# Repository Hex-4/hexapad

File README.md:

# Hexapad

A DIY macropad made for the [Hack Club](https://hack.club) [Hackpad](https://hackpad.hackclub.com) program! It's got 16 Cherry MX switches, a "jewel" of 3 THT NeoPixels, a rotary encoder, and an OLED screen. A I/O expander is used to make everything work. This repo holds the PCB design, case design, and KMK firmware.

## Making it

This was my _first time_ doing... most of this. I've dabbled in mechanical keyboards before (I'm typing this on one right now!) but I've never touched PCB design or CAD. Therefore, I made the perfectly rational decision to YOLO it and try not to mess up. Thankfully, it went quite well! I think. I picked up KiCad really quickly, and the community (#hackpad on the Hack Club Slack) was super helpful. OnShape was harder to grasp but I think I kinda get it now? The firmware was super easy thanks to KMK, all I really had to do was paste in a few things from the docs.

For the schematic, I wired up the matrix (easy enough) directly to the microcontroller - a Seeed Studio Xiao RP2040. As I'm writing this I've realized I probably should have skipped the INT pin on the I/O expander and used that for the NeoPixels instead but oh well. To accomodate my rotary encoder and RGB I added a PCF8574A I/O expander, which was a little tricky to wire but I think I got it. Then I added my OLED display, my NeoPixels... and then took a three-week long break from the project. 

After my break, I opened up the PCB editor and started cooking! It was actually really easy - all I had to do was arrange my parts nicely and add some graphics. Then I ran the FreeRouting autorouter which GREATLY speeded up my process.
With that done, I exported the 3D model of the PCB and put it into - oh wait. I don't have a CAD program of choice ¯\\\_(ツ)\_/¯

Following some recommendations from Hack Clubbers, I picked OnShape. It was super confusing at first, with all the mounting styles, different measurements, and fasteners. I ended up using a fully 3D printed sandwich mount but dropping the top plate. I sketched out a 102 x 102mm square (the size of my pcb + 2mm) then offset it by 12mm. I then added holes and hexagonal holes in the corners to accomodate M4 screws and nuts. I then made my plate with [Keyboard Layout Editor](https://keyboard-layout-editor.com/) and the [keeb.io plate generator](https://plate.keeb.io/) with a fillet of 0mm so nothing weird happened when I moved it around. Then after some quick sketching and decoration, the Hexapad was done! I made sure to import the PCB model and checked for fit. You can check out my design [here.](https://cad.onshape.com/documents/2133e09e1f245de59bbe7858/w/b4533889f6300572d81eb032/e/b0c575e6e2f32d509dfa7b54) _(note: this design's PCB model is outdated. I moved some things around to give more clearance.)_

Finally, I coded up the firmware. I don't really have much to say for this, it was just importing various modules and setting them up, then choosing things for the keymap.

Overall, I'm really happy with this project! It was really fun making everything, and I think I learnt some really useful skills. Of course, I haven't gotten it yet and I have no idea if it'll work... but let's hope it does.

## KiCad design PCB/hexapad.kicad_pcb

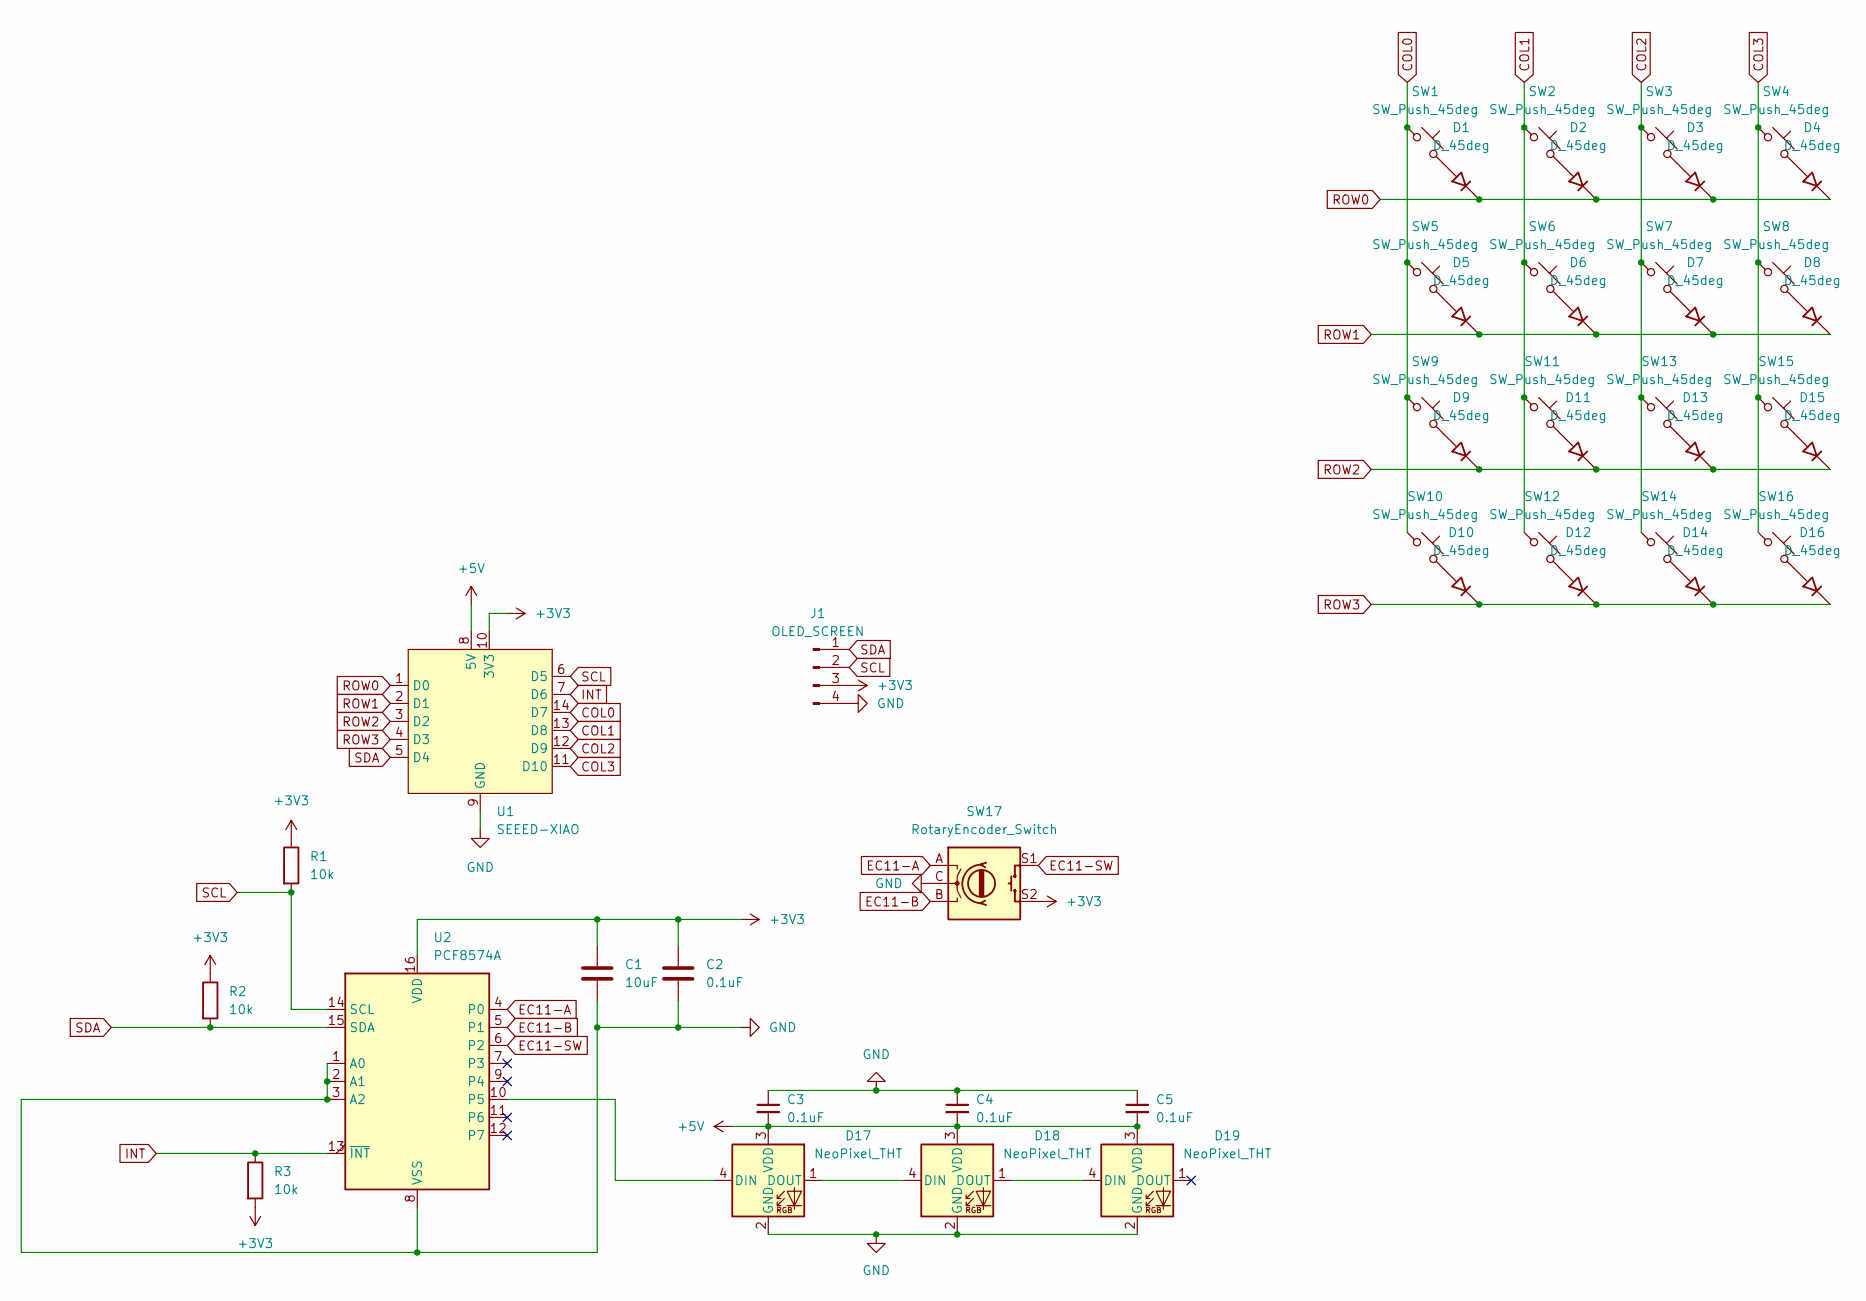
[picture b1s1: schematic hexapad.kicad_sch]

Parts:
C1: 10uF; C_Radial_D5.0mm_H7.0mm_P2.00mm
C2, C3, C4, C5: 0.1uF; C_Radial_D5.0mm_H7.0mm_P2.00mm
D1, D2, D3, D4, D5, D6, D7, D8, D9, D10, D11, D12, D13, D14, D15, D16: D_45deg; D_DO-35_SOD27_P7.62mm_Horizontal
D17, D18, D19: NeoPixel_THT; LED_D5.0mm-4_RGB
J1: OLED_SCREEN
R1, R2, R3: 10k
SW1, SW2, SW3, SW4, SW5, SW6, SW7, SW8, SW9, SW10, SW11, SW12, SW13, SW14, SW15, SW16: SW_Push_45deg
SW17: RotaryEncoder_Switch
U1: SEEED-XIAO; XIAO-14P-THT-2.54-21x17.8MM
U2: PCF8574A; DIP-16_W7.62mm

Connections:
+3V3: C1.1, C2.1, J1.3, R1.1, R2.1, R3.2, SW17.S2, U1.10 (3V3), U2.16 (VDD)
+5V: C3.2, C4.2, C5.2, D17.3 (VDD), D18.3 (VDD), D19.3 (VDD), U1.8 (5V)
COL0: SW1.1, SW5.1, SW9.1, SW10.1, U1.14 (D7)
COL1: SW2.1, SW6.1, SW11.1, SW12.1, U1.13 (D8)
COL2: SW3.1, SW7.1, SW13.1, SW14.1, U1.12 (D9)
COL3: SW4.1, SW8.1, SW15.1, SW16.1, U1.11 (D10)
EC11-A: SW17.A, U2.4 (P0)
EC11-B: SW17.B, U2.5 (P1)
EC11-SW: SW17.S1, U2.6 (P2)
GND: C1.2, C2.2, C3.1, C4.1, C5.1, D17.2 (GND), D18.2 (GND), D19.2 (GND), J1.4, SW17.C, U1.9 (GND), U2.1 (A0), U2.2 (A1), U2.3 (A2), U2.8 (VSS)
INT: R3.1, U1.7 (D6), U2.13 (~INT)
unnamed: D1.2 (A), SW1.2
unnamed: D2.2 (A), SW2.2
unnamed: D3.2 (A), SW3.2
unnamed: D4.2 (A), SW4.2
unnamed: D5.2 (A), SW5.2
unnamed: D6.2 (A), SW6.2
unnamed: D7.2 (A), SW7.2
unnamed: D8.2 (A), SW8.2
unnamed: D9.2 (A), SW9.2
unnamed: D10.2 (A), SW10.2
unnamed: D11.2 (A), SW11.2
unnamed: D12.2 (A), SW12.2
unnamed: D13.2 (A), SW13.2
unnamed: D14.2 (A), SW14.2
unnamed: D15.2 (A), SW15.2
unnamed: D16.2 (A), SW16.2
unnamed: D17.4 (DIN), U2.10 (P5)
unnamed: D17.1 (DOUT), D18.4 (DIN)
unnamed: D18.1 (DOUT), D19.4 (DIN)
ROW0: D1.1 (K), D2.1 (K), D3.1 (K), D4.1 (K), U1.1 (D0)
ROW1: D5.1 (K), D6.1 (K), D7.1 (K), D8.1 (K), U1.2 (D1)
ROW2: D9.1 (K), D11.1 (K), D13.1 (K), D15.1 (K), U1.3 (D2)
ROW3: D10.1 (K), D12.1 (K), D14.1 (K), D16.1 (K), U1.4 (D3)
SCL: J1.2, R1.2, U1.6 (D5), U2.14 (SCL)
SDA: J1.1, R2.2, U1.5 (D4), U2.15 (SDA)

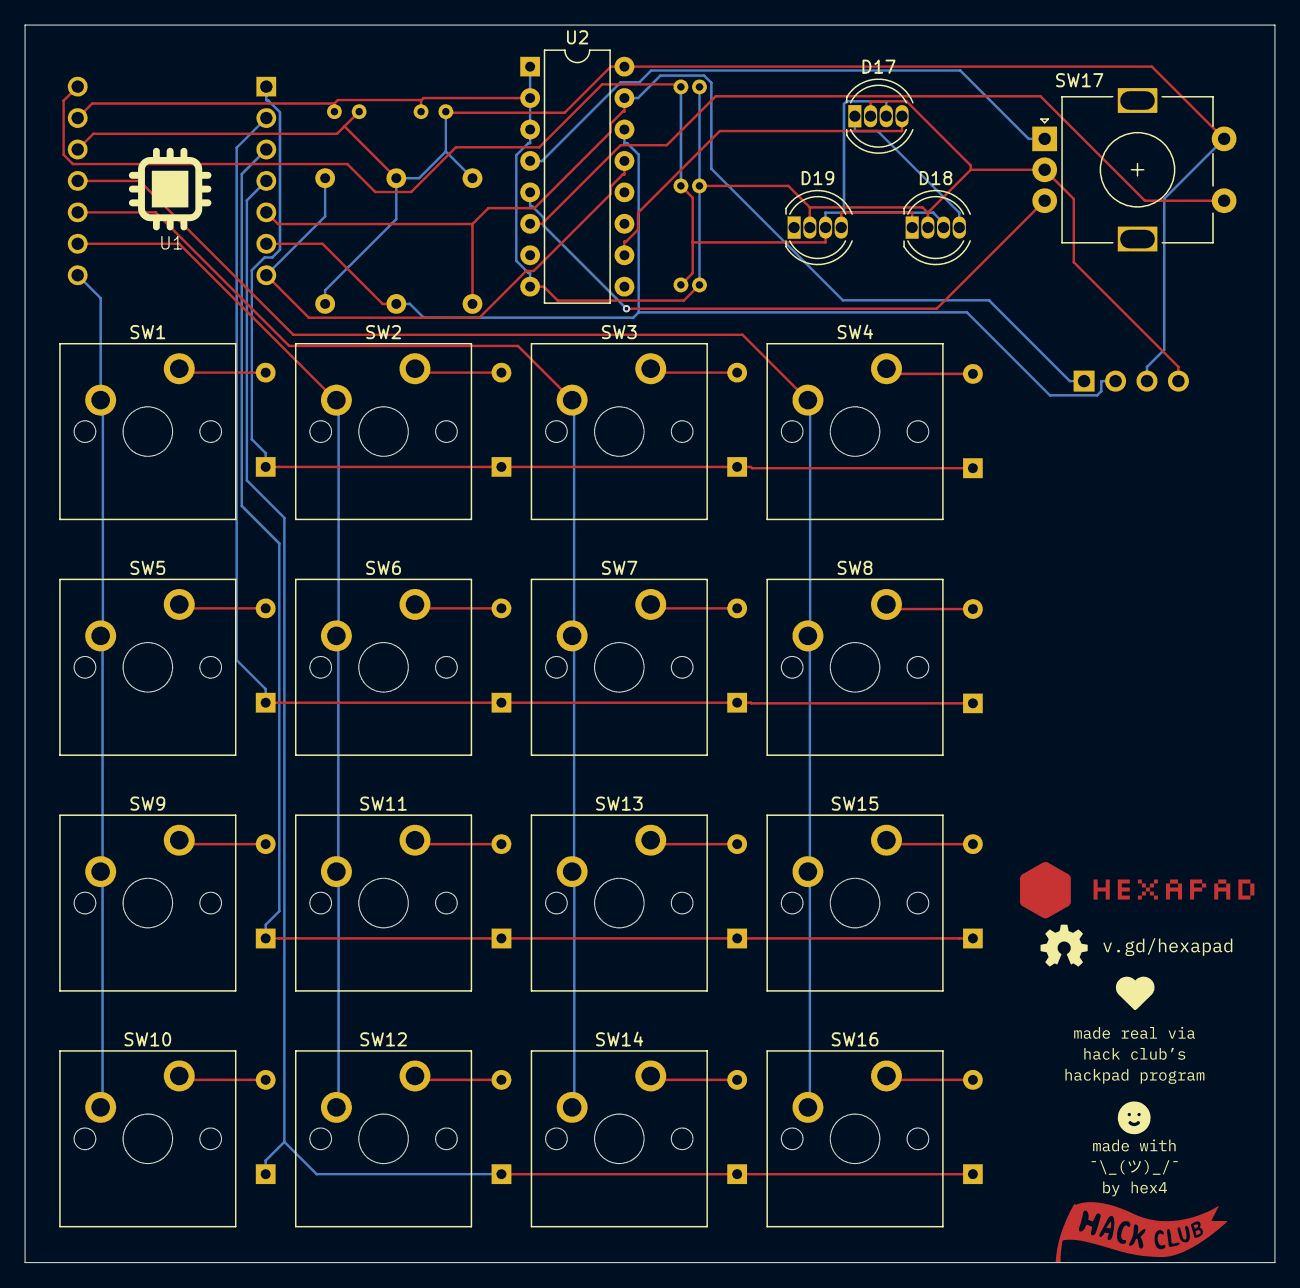
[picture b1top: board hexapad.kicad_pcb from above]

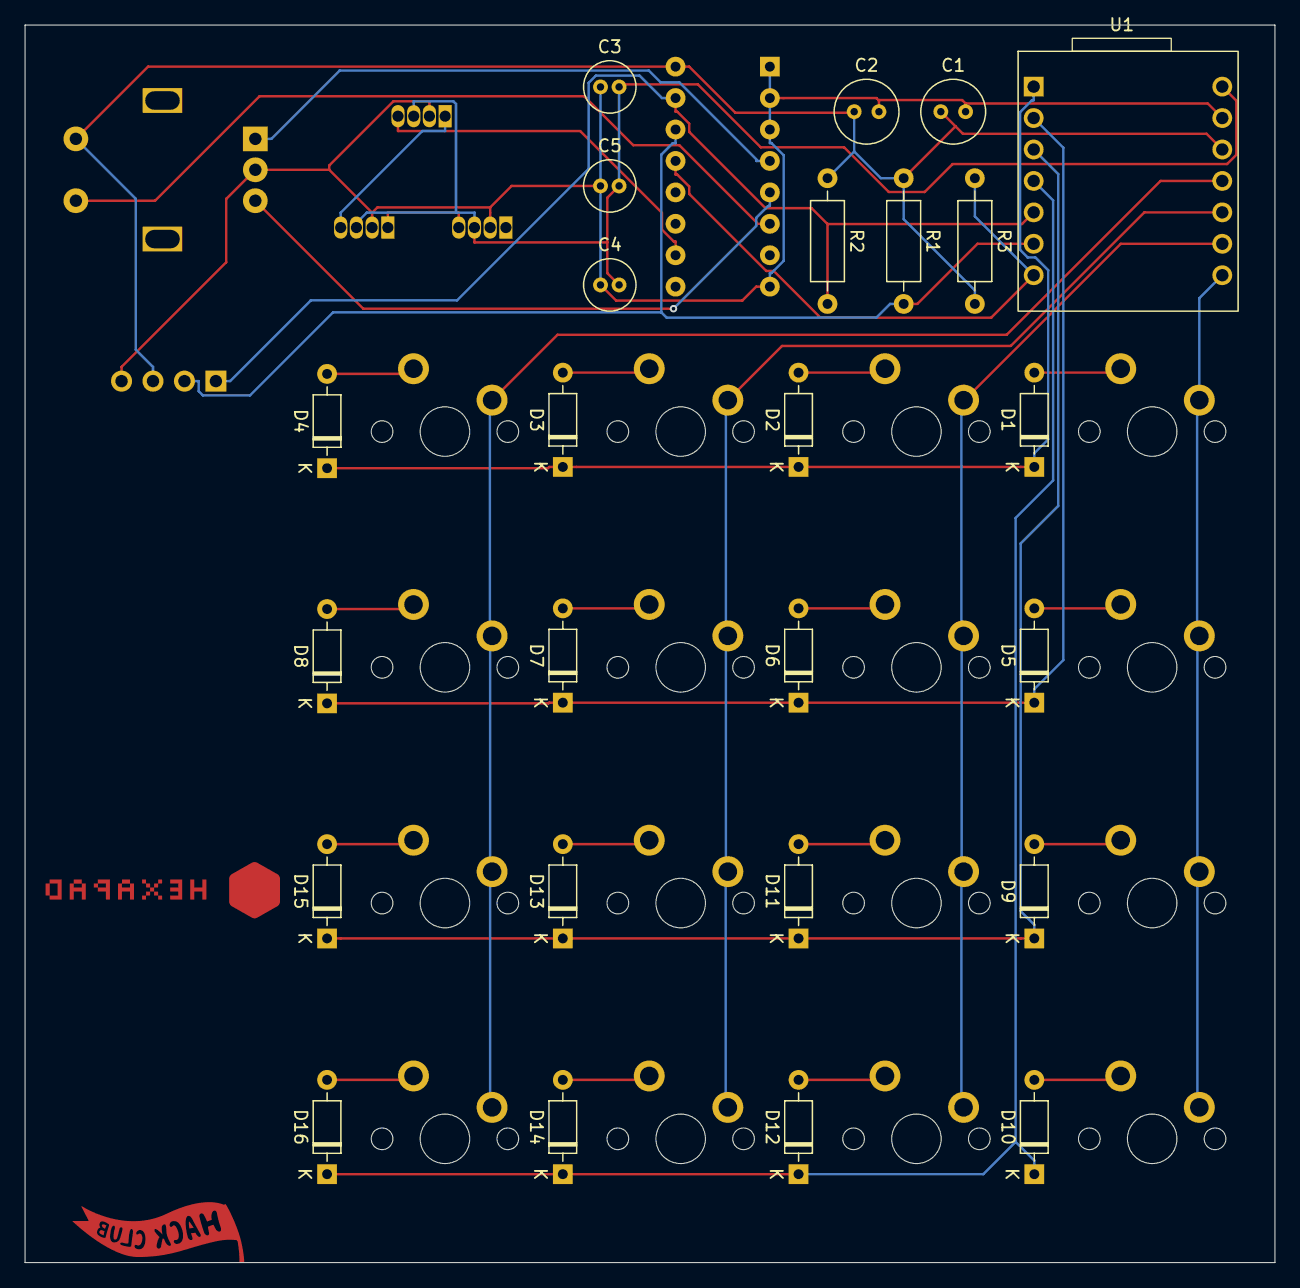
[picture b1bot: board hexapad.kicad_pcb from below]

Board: 2 copper layers, 101.0 x 100.0 mm, 47 parts (25 on the bottom side), 36 nets.

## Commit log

2024-09-18 init kicad project
2024-09-18 Add libraries as submodules
2024-09-18 Add libraries
2024-09-18 get rid of ai03 guide, i'm jumping right in
2024-09-21 Switch to averse's XIAO libs
2024-10-05 a lot lol
2024-10-10 a lot lol, hopefully schematic is done
2024-10-10 fix neopixel spacing
2024-10-11 add ScottoKeebs lib
2024-10-13 kinda finalize pcb and restructure project
2024-10-13 Modify gitignore, start on READMEs
2024-10-14 a bunch of firmware stuff
2024-10-14 finish firmware?
2024-10-14 add cad files
2024-10-18 actually good readme
2024-10-18 fix readme
2024-10-18 fix readme, again
